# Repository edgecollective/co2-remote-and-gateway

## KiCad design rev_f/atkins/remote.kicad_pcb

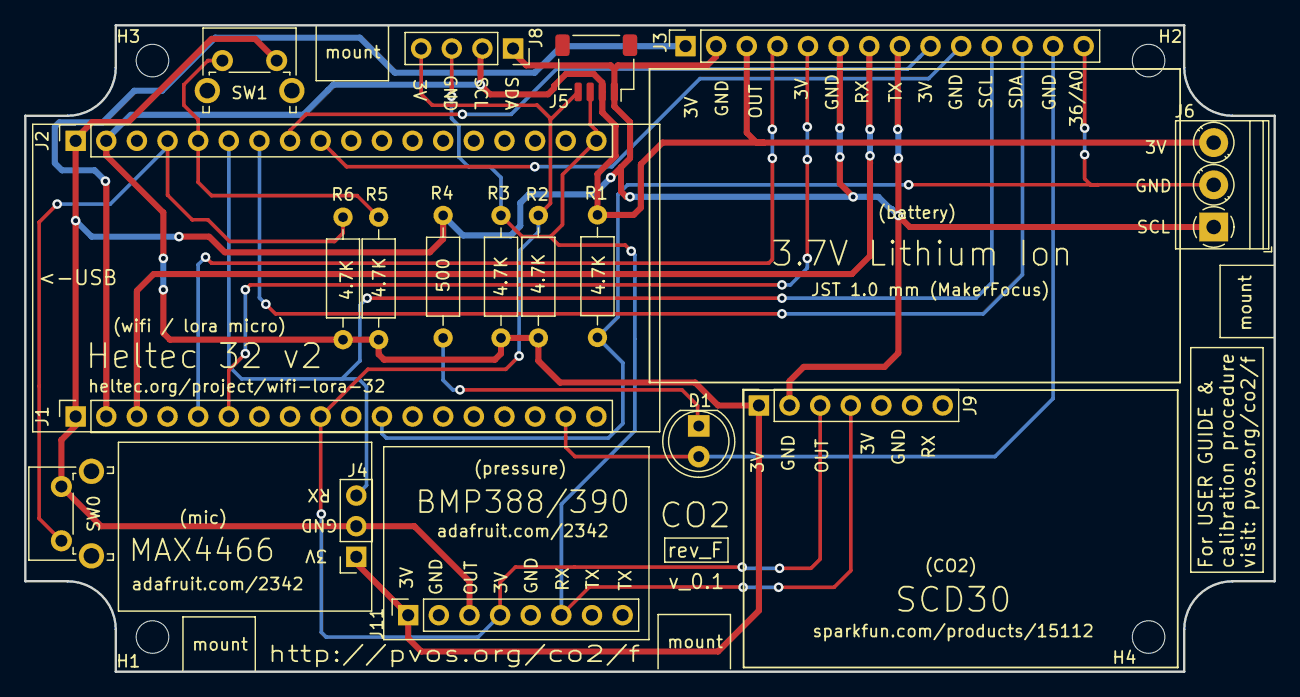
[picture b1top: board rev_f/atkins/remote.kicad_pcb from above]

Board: 2 copper layers, 103.6 x 53.6 mm, 22 parts (0 on the bottom side), 17 nets.

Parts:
D1: LED; LED_D5.0mm
H1, H2, H3, H4: MountingHole; MountingHole_2.7mm_M2.5
J1, J2: Conn_01x18_Female; PinSocket_1x18_P2.54mm_Vertical
J3: Conn_01x14_Female; PinSocket_1x14_P2.54mm_Vertical
J4: Conn_01x03_Female; PinSocket_1x03_P2.54mm_Vertical
J5: Conn_01x04_Female; JST_SH_SM04B-SRSS-TB_1x04-1MP_P1.00mm_Horizontal
J6: Screw_Terminal_01x03; TerminalBlock_Phoenix_PT-1,5-3-3.5-H_1x03_P3.50mm_Horizontal
J8: Conn_01x04_Female; PinSocket_1x04_P2.54mm_Vertical
J9: SCD30; PinSocket_1x07_P2.54mm_Vertical
J11: BME390; PinSocket_1x08_P2.54mm_Vertical
R1, R2, R3: R; R_Axial_DIN0207_L6.3mm_D2.5mm_P10.16mm_Horizontal
R4: 500R; R_Axial_DIN0207_L6.3mm_D2.5mm_P10.16mm_Horizontal
R5, R6: 4.7K; R_Axial_DIN0207_L6.3mm_D2.5mm_P10.16mm_Horizontal
SW0, SW1: SW_Push; SW_Tactile_SPST_Angled_PTS645Vx58-2LFS

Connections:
5V: J1.2, J3.1
17: D1.2, J1.17, J3.13
23: J1.11, J3.14, J6.2, R1.2
34_ADC6_DIO2: J2.8, J3.9
35_ADC7_DIO1: J2.9, J3.10
36_A0: J2.4, R6.2, SW0.1
37_A1: J2.5, R5.2, SW1.1
38_A2: J2.6, J3.11, J4.3
39_A3: J2.7, J3.12
+3V3: J2.2, J3.3, J4.1, J5.2, J6.3, J8.2, J9.1, J11.1, R1.1, R2.1, R3.1, R5.1, R6.1
GND: J1.1, J2.1, J3.2, J3.6, J3.8, J4.2, J5.1, J6.1, J8.1, J9.2, J11.3, R4.2, SW0.2, SW1.2
unnamed: D1.1, R4.1
RX: J1.5, J3.4
SCL: J1.9, J5.4, J8.4, J9.3, J11.4, R2.2
SDA: J2.18, J5.3, J8.3, J9.4, J11.6, R3.2
TX: J1.6, J3.5
VEXT: J1.3, J3.7

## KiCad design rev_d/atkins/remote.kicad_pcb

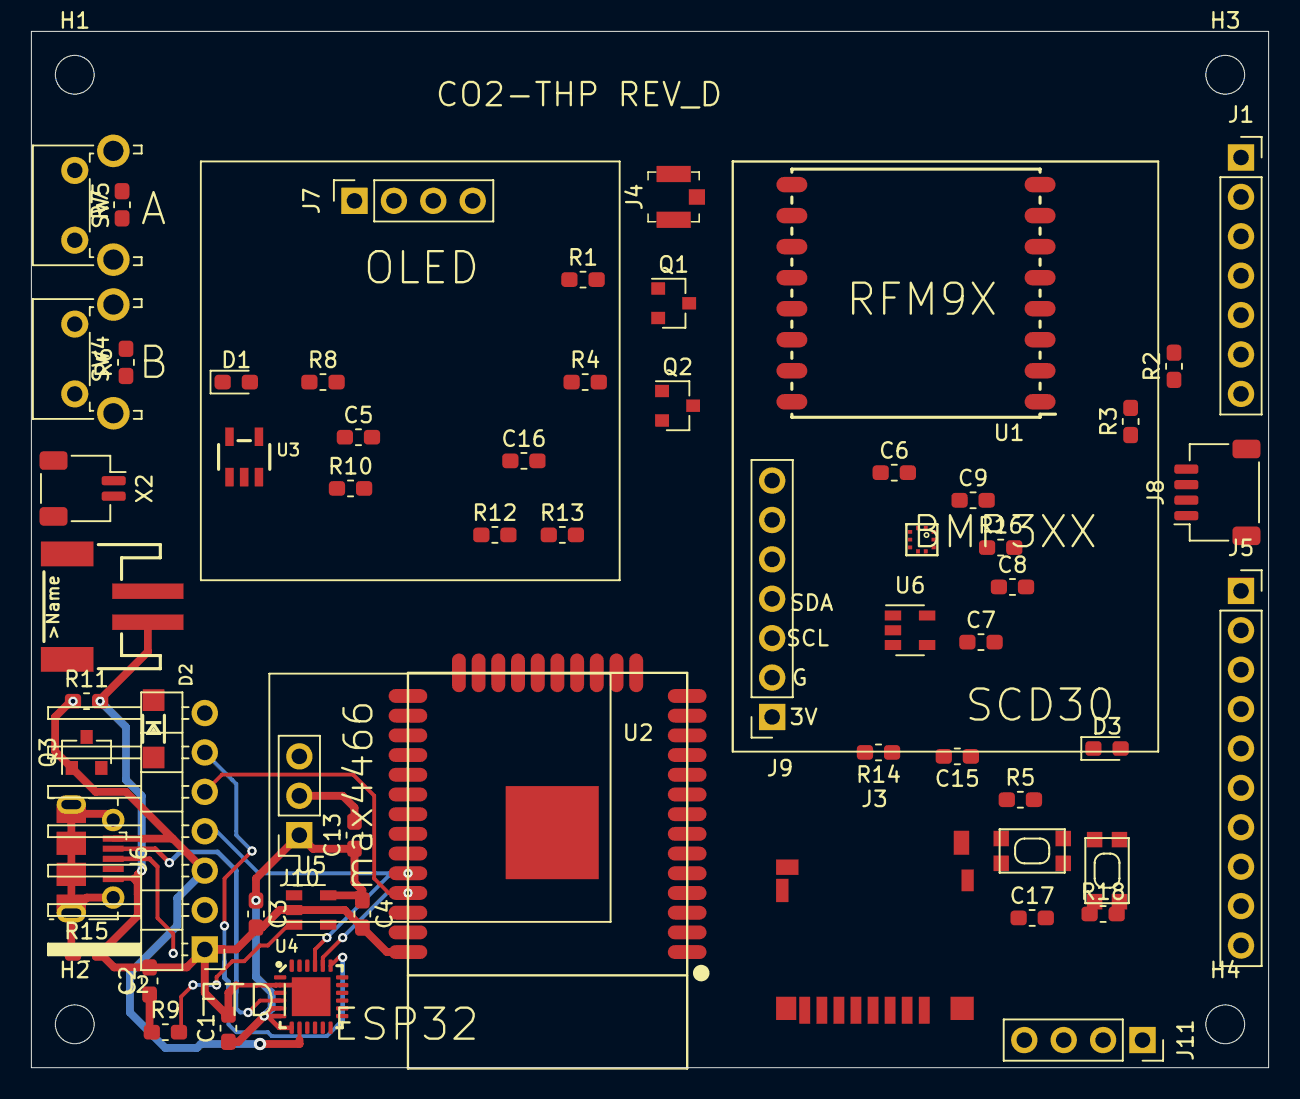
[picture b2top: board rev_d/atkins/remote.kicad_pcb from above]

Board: 2 copper layers, 79.8 x 66.8 mm, 64 parts (0 on the bottom side), 44 nets.

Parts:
C1, C2, C3, C6, C7: 10uF; C_0603_1608Metric_Pad1.05x0.95mm_HandSolder
C4, C8: 1uF; C_0603_1608Metric_Pad1.05x0.95mm_HandSolder
C5, C15, C17: C; C_0603_1608Metric_Pad1.05x0.95mm_HandSolder
C9, C13, C16: 0.1uF; C_0603_1608Metric_Pad1.05x0.95mm_HandSolder
D1, D3: LED; LED_0603_1608Metric_Pad1.05x0.95mm_HandSolder
D2: MBR120; SOD-123
H1, H2, H3, H4: MountingHole; MountingHole_2.5mm
J1: Conn_01x07_Female; PinSocket_1x07_P2.54mm_Vertical
J2: Conn_01x07_Female; PinHeader_1x07_P2.54mm_Horizontal
J3: Micro_SD_Card; DM3D-SF
J4: U_FL-R-SMT-1_10_; Coax_Conn_U.FL
J5: Conn_01x10_Female; PinSocket_1x10_P2.54mm_Vertical
J6: USB_B_Micro; USB_Micro-B_Molex-105017-0001
J7, J11: Conn_01x04_Female; PinSocket_1x04_P2.54mm_Vertical
J8: Conn_01x04_Male; JST_SH_SM04B-SRSS-TB_1x04-1MP_P1.00mm_Horizontal
J9: SCD30; PinSocket_1x07_P2.54mm_Vertical
J10: Conn_01x03_Female; PinSocket_1x03_P2.54mm_Vertical
Q1, Q2: Q_NPN_BEC; SOT-23
Q3: Q_PMOS_GSD - DMG3415U; SOT-23
R1, R2, R3, R4: R; R_0603_1608Metric_Pad1.05x0.95mm_HandSolder
R5, R6, R7, R10: 10K; R_0603_1608Metric_Pad1.05x0.95mm_HandSolder
R8: 1K; R_0603_1608Metric_Pad1.05x0.95mm_HandSolder
R9, R11, R16: 100K; R_0603_1608Metric_Pad1.05x0.95mm_HandSolder
R12, R13: 10M; R_0603_1608Metric_Pad1.05x0.95mm_HandSolder
R14, R15: 0 Ohm; R_0603_1608Metric_Pad1.05x0.95mm_HandSolder
R18: 500 Ohm; R_0603_1608Metric_Pad1.05x0.95mm_HandSolder
SW2, SW3: SPST_TACT-KMR2; KMR2
SW4, SW5: SW_Push; SW_Tactile_SPST_Angled_PTS645Vx58-2LFS
U1: RFM95HW; RFM95
U2: ESP32-WROOM
U3: MCP73831_2; SOT23-5
U4: CP2104; QFN24_4MM_SMSC
U5, U6: AP2112K-3.3; SOT-23-5
X1: CON_JST_PH_2PIN; JSTPH2
X2: CON_JST_PH_2PIN; JST_SH_SM02B-SRSS-TB_1x02-1MP_P1.00mm_Horizontal
u18: BMP388

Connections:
0: J11.1, Q1.3, SW2.2, SW2.4, U2.25
2: J11.2, U2.24
4: J11.3, U2.26
+3V3: C1.1, C3.1, C4.1, C7.1, C8.1, C9.1, C13.1, J1.5, J3.4, J7.2, J8.2, J9.1, J10.1, R2.1, R3.1, R6.1, R7.1, U1.13, U2.2, U4.5, U4.6, U4.7, U5.5, U6.5, u18.1, u18.10
A0_26_DAC0: J1.2, U2.11
A1_25_DAC1: J1.1, U2.10
A2_34: R7.2, SW5.2, U2.6
A7_32: R6.2, SW4.2, U2.8
A8_15: J10.3, U2.23
A11_12: D3.2, U2.14
A13_35: C16.1, R12.2, R13.1, U2.7
ANA: J4.2, U1.9
DTR: J2.7, Q1.2, R4.2, U4.23
GND: C1.2, C2.2, C3.2, C4.2, C5.2, C6.2, C7.2, C8.2, C9.2, C13.2, C15.2, C16.2, C17.2, J1.4, J2.1, J3.6, J4.1, J6.5, J7.1, J8.1, J9.2, J10.2, R11.2, R13.2, R15.2, R18.1, SW2.1, SW2.3, SW3.1, SW3.3, SW4.1, SW5.1, U1.1, U1.8, U1.10, U2.1, U2.38, U2.39, U4.2, U4.THERM, U5.2, U6.2, X1.1, X2.1, u18.3, u18.8, u18.9
MISO: J3.7, U1.2, U2.31
MOSI: J3.3, U1.3, U2.30
unnamed: C2.1, C6.1, Q3.2, R9.1, R16.1, U5.1, U6.1
unnamed: C15.1, R14.1
unnamed: D1.1, R8.2
unnamed: D3.1, R18.2
unnamed: J3.9, R14.2
unnamed: J6.2, U4.4
unnamed: J6.3, U4.3
unnamed: J6.6, R15.1
unnamed: Q1.1, R1.1
unnamed: Q2.1, R4.1
unnamed: R5.2, SW3.2, SW3.4
unnamed: R8.1, U3.1
unnamed: R9.2, U5.3
unnamed: R10.1, U3.2
unnamed: R10.2, U3.5
unnamed: R16.2, U6.3
RESET: C17.1, Q2.3, R5.1, U2.3
RTS: J2.6, Q2.2, R1.2, U4.19
RXD0: J2.4, U2.34, U4.21
SCK: J3.5, U1.4, U2.29
SCL: J1.7, J7.3, J8.4, J9.3, R2.2, U2.36, u18.2
SDA: J1.6, J7.4, J8.3, J9.4, R3.2, U2.37, u18.4
TXD0: J2.5, U2.35, U4.20
VBAT: C5.1, J11.4, Q3.3, R12.1, U3.3, X1.2, X2.2
VBUS: D1.2, J2.3, J6.1, Q3.1, R11.1, U3.4, U4.8
lora_cs: U1.5, U2.28
lora_dio0: U1.14, U2.27
lora_dio1: U1.15, U2.13, U2.16

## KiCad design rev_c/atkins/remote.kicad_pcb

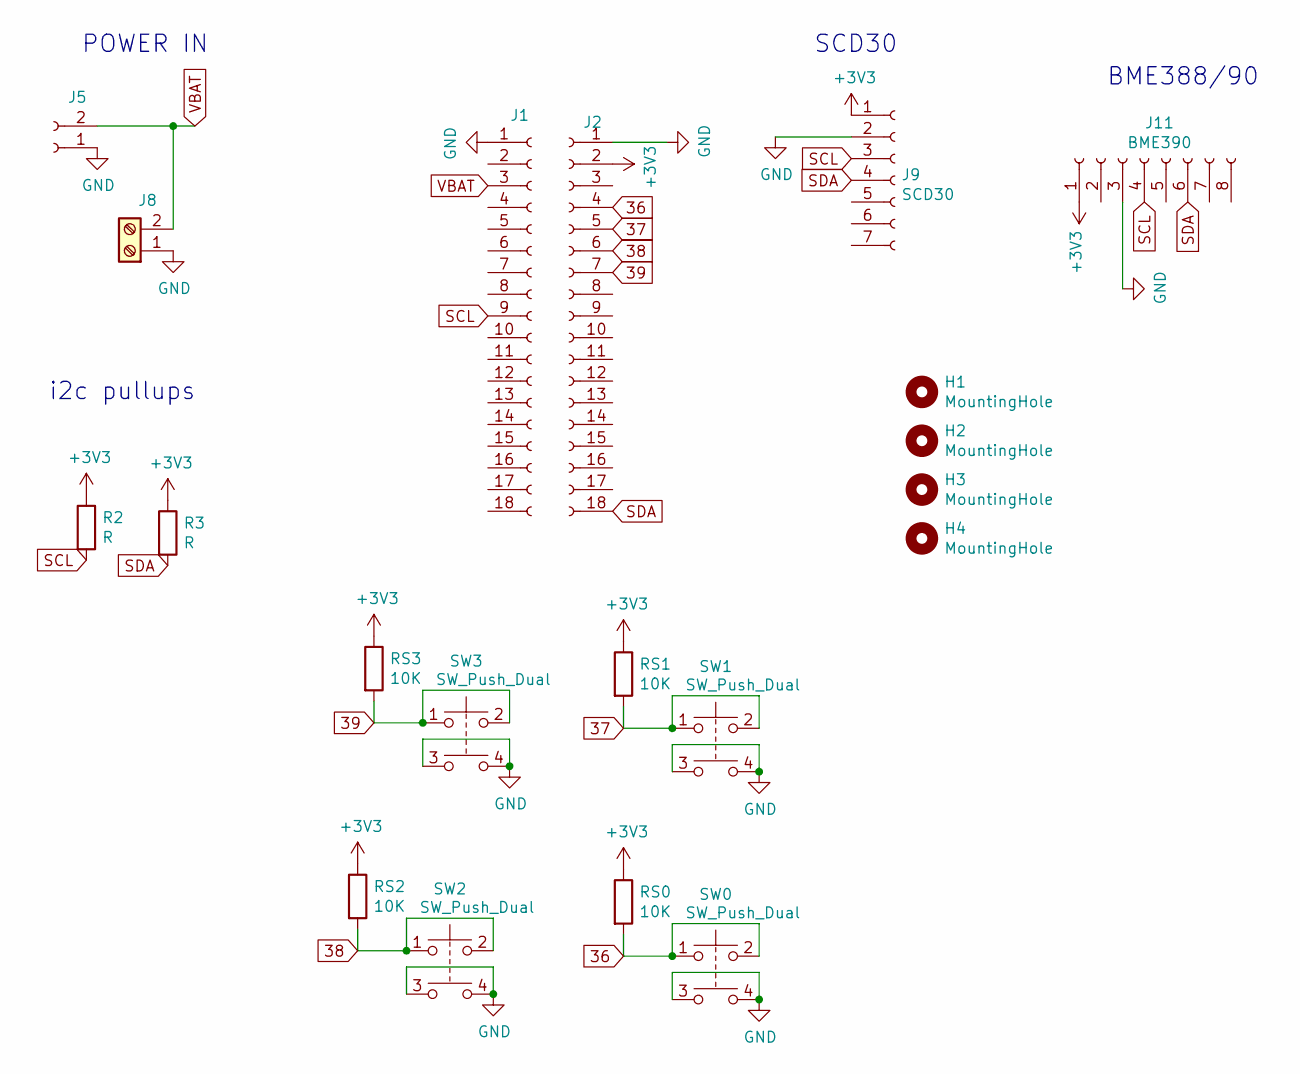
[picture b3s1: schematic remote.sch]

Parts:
H1, H2, H3, H4: MountingHole; MountingHole_2.7mm_M2.5
J1, J2: Conn_01x18_Female; PinSocket_1x18_P2.54mm_Vertical
J5: Conn_01x02_Female; PinSocket_1x02_P2.54mm_Vertical
J8: Screw_Terminal_01x02; TerminalBlock_Phoenix_MKDS-1,5-2_1x02_P5.00mm_Horizontal
J9: SCD30; PinSocket_1x07_P2.54mm_Vertical
J11: BME390; PinSocket_1x08_P2.54mm_Vertical
R2, R3: R; R_Axial_DIN0207_L6.3mm_D2.5mm_P10.16mm_Horizontal
RS0, RS1, RS2, RS3: 10K; R_Axial_DIN0207_L6.3mm_D2.5mm_P10.16mm_Horizontal
SW0, SW1, SW2, SW3: SW_Push_Dual; SW_TH_Tactile_Omron_B3F-10xx

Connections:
36: J2.4, RS0.2, SW0.1, SW0.2
37: J2.5, RS1.2, SW1.1, SW1.2
38: J2.6, RS2.2, SW2.1, SW2.2
39: J2.7, RS3.2, SW3.1, SW3.2
+3V3: J2.2, J9.1, J11.1, R2.1, R3.1, RS0.1, RS1.1, RS2.1, RS3.1
GND: J1.1, J2.1, J5.1, J8.1, J9.2, J11.3, SW0.3, SW0.4, SW1.3, SW1.4, SW2.3, SW2.4, SW3.3, SW3.4
SCL: J1.9, J9.3, J11.4, R2.2
SDA: J2.18, J9.4, J11.6, R3.2
VBAT: J1.3, J5.2, J8.2

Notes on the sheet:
POWER IN
i2c pullups
SCD30
BME388/90

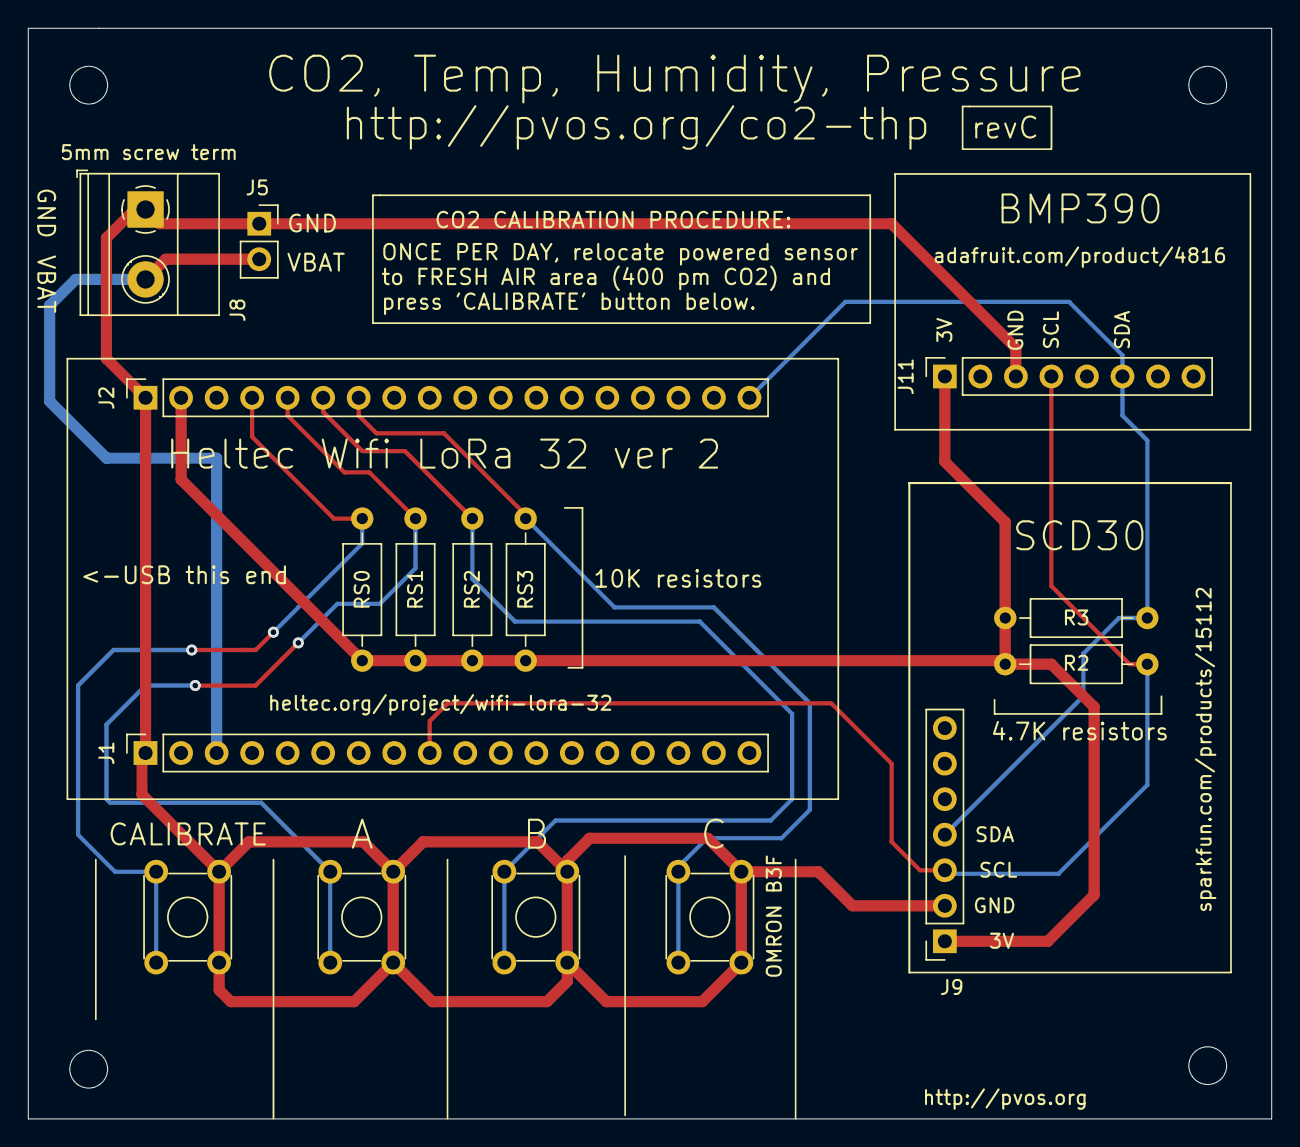
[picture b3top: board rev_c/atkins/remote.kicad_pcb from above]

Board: 2 copper layers, 88.9 x 78.0 mm, 20 parts (0 on the bottom side), 9 nets.

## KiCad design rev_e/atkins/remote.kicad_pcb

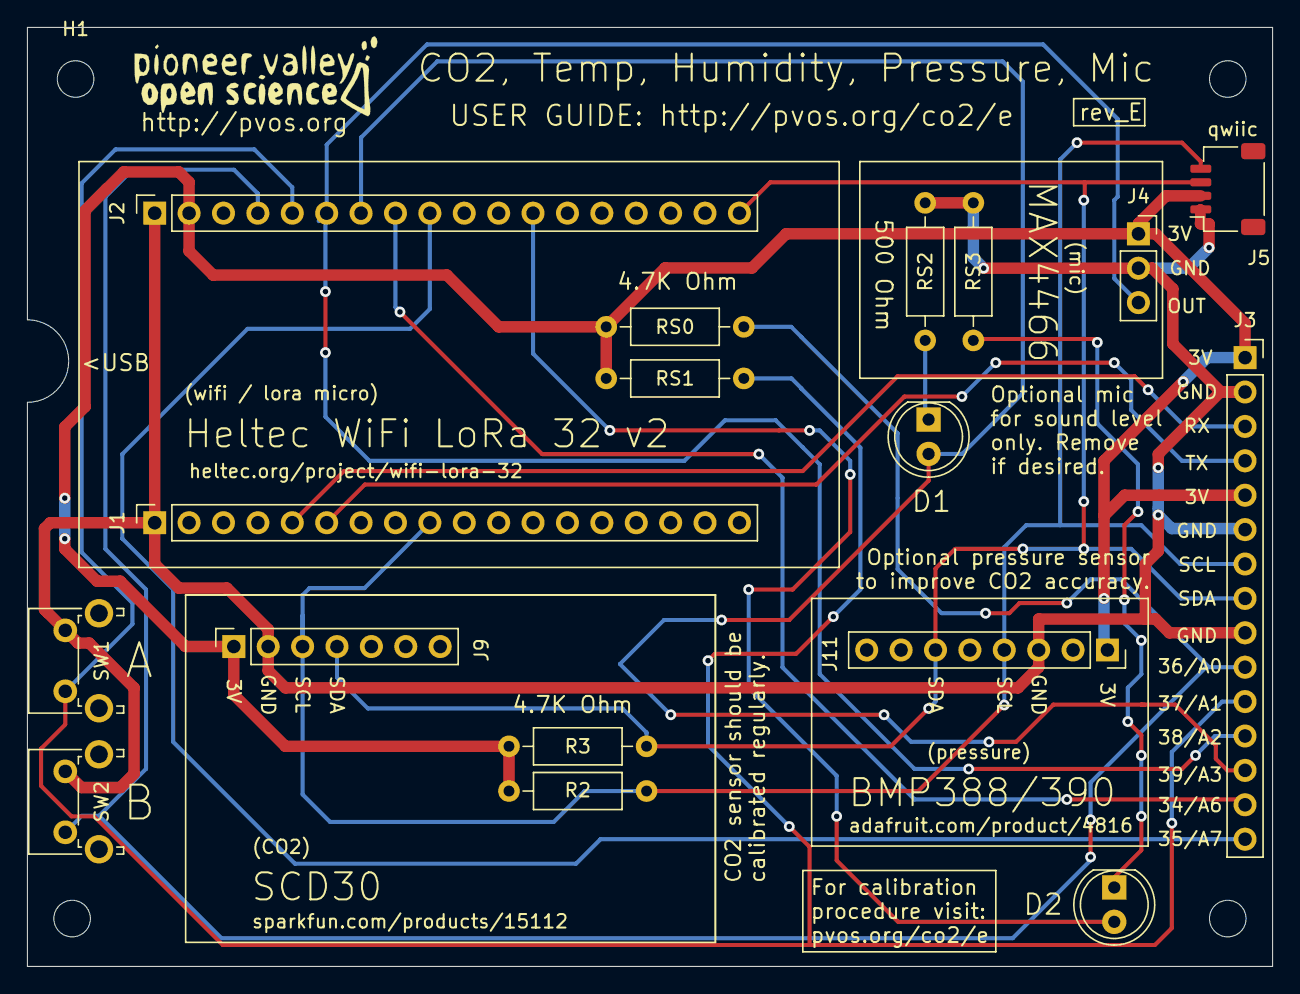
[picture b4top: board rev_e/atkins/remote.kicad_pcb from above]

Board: 2 copper layers, 91.9 x 69.3 mm, 21 parts (0 on the bottom side), 15 nets.

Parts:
D1, D2: LED; LED_D5.0mm
H1, H2, H3, H4: MountingHole; MountingHole_2.7mm_M2.5
J1, J2: Conn_01x18_Female; PinSocket_1x18_P2.54mm_Vertical
J3: Conn_01x15_Female; PinSocket_1x15_P2.54mm_Vertical
J4: Conn_01x03_Female; PinSocket_1x03_P2.54mm_Vertical
J5: Conn_01x04_Female; JST_SH_SM04B-SRSS-TB_1x04-1MP_P1.00mm_Horizontal
J9: SCD30; PinSocket_1x07_P2.54mm_Vertical
J11: BME390; PinSocket_1x08_P2.54mm_Vertical
R2, R3: R; R_Axial_DIN0207_L6.3mm_D2.5mm_P10.16mm_Horizontal
RS0, RS1: 10K; R_Axial_DIN0207_L6.3mm_D2.5mm_P10.16mm_Horizontal
RS2, RS3: 500R; R_Axial_DIN0207_L6.3mm_D2.5mm_P10.16mm_Horizontal
SW1, SW2: SW_Push; SW_Tactile_SPST_Angled_PTS645Vx58-2LFS

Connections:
25_LED: D2.2, J2.12
34_A6: J2.8, J3.14
35_A7: J2.9, J3.15
36_A0: J2.4, J3.10, RS0.2, SW2.1
37_A1: J2.5, J3.11, RS1.2, SW1.1
38_A2: J2.6, J3.12, J4.3
39_A3: D1.2, J2.7, J3.13
+3V3: J2.2, J3.1, J3.5, J4.1, J5.2, J9.1, J11.1, R2.1, R3.1, RS0.1, RS1.1
GND: J1.1, J2.1, J3.2, J3.6, J3.9, J4.2, J5.1, J9.2, J11.3, RS2.2, RS3.2, SW1.2, SW2.2
unnamed: D1.1, RS2.1
unnamed: D2.1, RS3.1
RX: J1.5, J3.3
SCL: J1.9, J3.7, J5.4, J9.3, J11.4, R2.2
SDA: J2.18, J3.8, J5.3, J9.4, J11.6, R3.2
TX: J1.6, J3.4

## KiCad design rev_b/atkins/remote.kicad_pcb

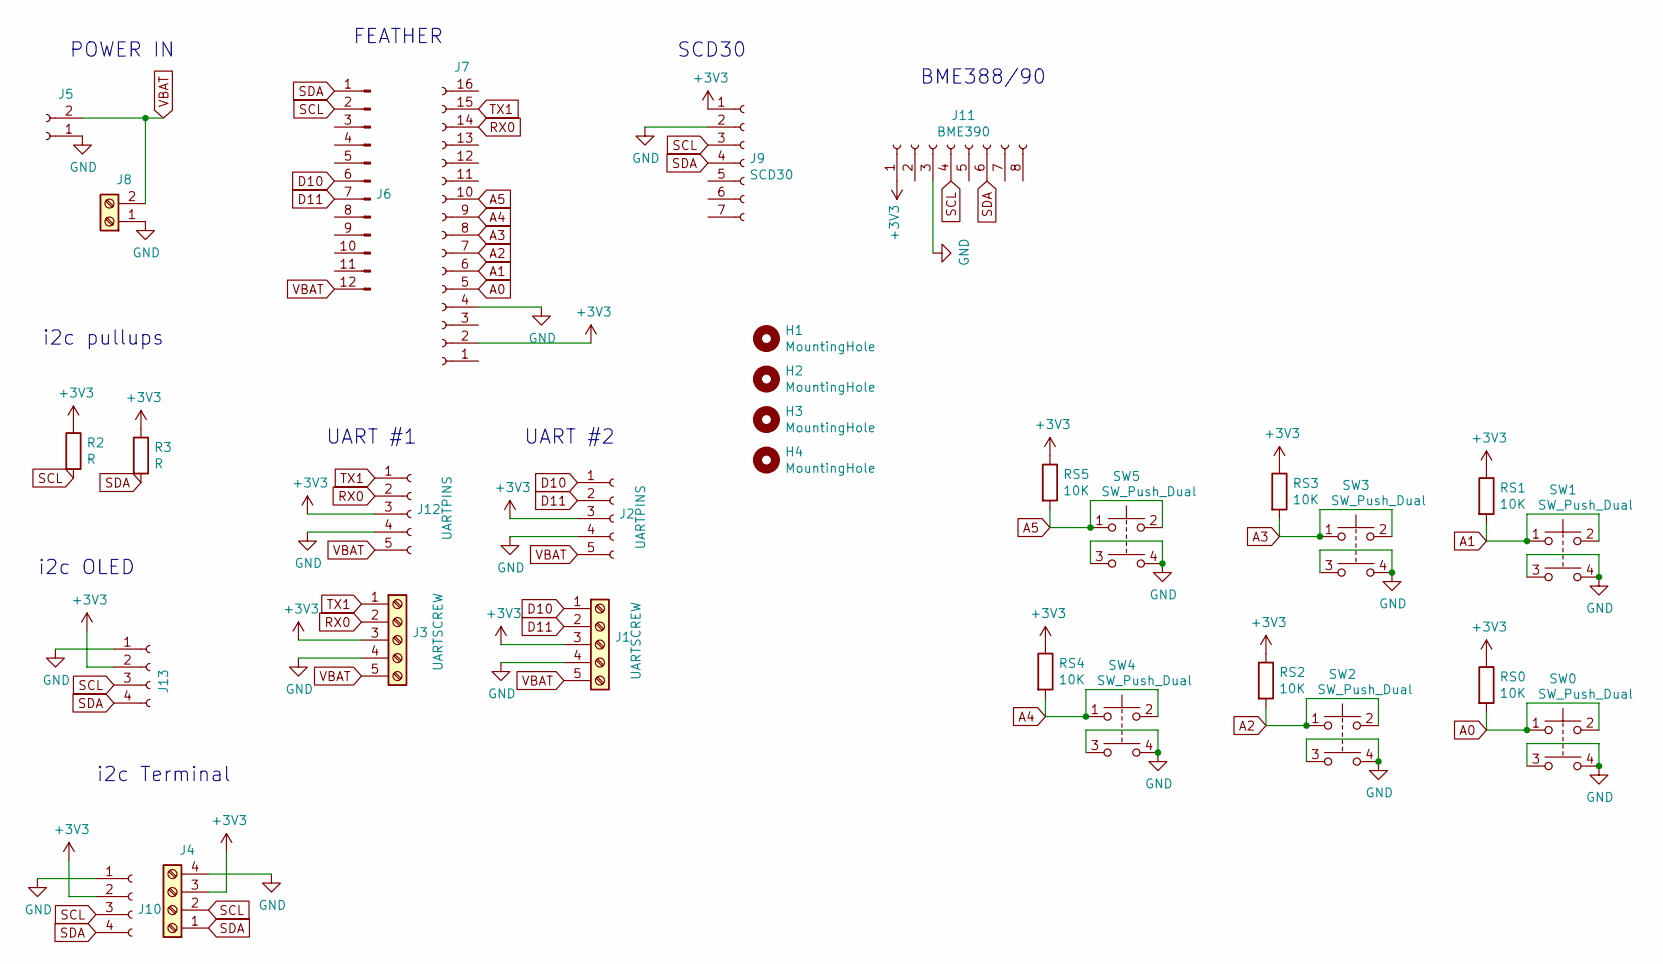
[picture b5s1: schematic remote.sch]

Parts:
H1, H2, H3, H4: MountingHole; MountingHole_2.7mm_M2.5
J1, J3: UARTSCREW; TerminalBlock_Phoenix_MKDS-1,5-5_1x05_P5.00mm_Horizontal
J2, J12: UARTPINS; PinSocket_1x05_P2.54mm_Vertical
J4: Screw_Terminal_01x04; TerminalBlock_Phoenix_MKDS-1,5-4_1x04_P5.00mm_Horizontal
J5: Conn_01x02_Female; PinSocket_1x02_P2.54mm_Vertical
J6: Conn_01x12_Male; PinSocket_1x12_P2.54mm_Vertical
J7: Conn_01x16_Female; PinSocket_1x16_P2.54mm_Vertical
J8: Screw_Terminal_01x02; TerminalBlock_Phoenix_MKDS-1,5-2_1x02_P5.00mm_Horizontal
J9: SCD30; PinSocket_1x07_P2.54mm_Vertical
J10, J13: Conn_01x04_Female; PinSocket_1x04_P2.54mm_Vertical
J11: BME390; PinSocket_1x08_P2.54mm_Vertical
R2, R3: R; R_Axial_DIN0207_L6.3mm_D2.5mm_P10.16mm_Horizontal
RS0, RS1, RS2, RS3, RS4, RS5: 10K; R_Axial_DIN0207_L6.3mm_D2.5mm_P10.16mm_Horizontal
SW0, SW1, SW2, SW3, SW4, SW5: SW_Push_Dual; SW_TH_Tactile_Omron_B3F-10xx

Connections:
+3V3: J1.3, J2.3, J3.3, J4.3, J7.2, J9.1, J10.2, J11.1, J12.3, J13.2, R2.1, R3.1, RS0.1, RS1.1, RS2.1, RS3.1, RS4.1, RS5.1
A0: J7.5, RS0.2, SW0.1, SW0.2
A1: J7.6, RS1.2, SW1.1, SW1.2
A2: J7.7, RS2.2, SW2.1, SW2.2
A3: J7.8, RS3.2, SW3.1, SW3.2
A4: J7.9, RS4.2, SW4.1, SW4.2
A5: J7.10, RS5.2, SW5.1, SW5.2
D10: J1.1, J2.1, J6.6
D11: J1.2, J2.2, J6.7
GND: J1.4, J2.4, J3.4, J4.4, J5.1, J7.4, J8.1, J9.2, J10.1, J11.3, J12.4, J13.1, SW0.3, SW0.4, SW1.3, SW1.4, SW2.3, SW2.4, SW3.3, SW3.4, SW4.3, SW4.4, SW5.3, SW5.4
RX0: J3.2, J7.14, J12.2
SCL: J4.2, J6.2, J9.3, J10.3, J11.4, J13.3, R2.2
SDA: J4.1, J6.1, J9.4, J10.4, J11.6, J13.4, R3.2
TX1: J3.1, J7.15, J12.1
VBAT: J1.5, J2.5, J3.5, J5.2, J6.12, J8.2, J12.5

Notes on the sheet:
UART #2
UART #1
POWER IN
FEATHER
i2c OLED
i2c Terminal
i2c pullups
SCD30
BME388/90

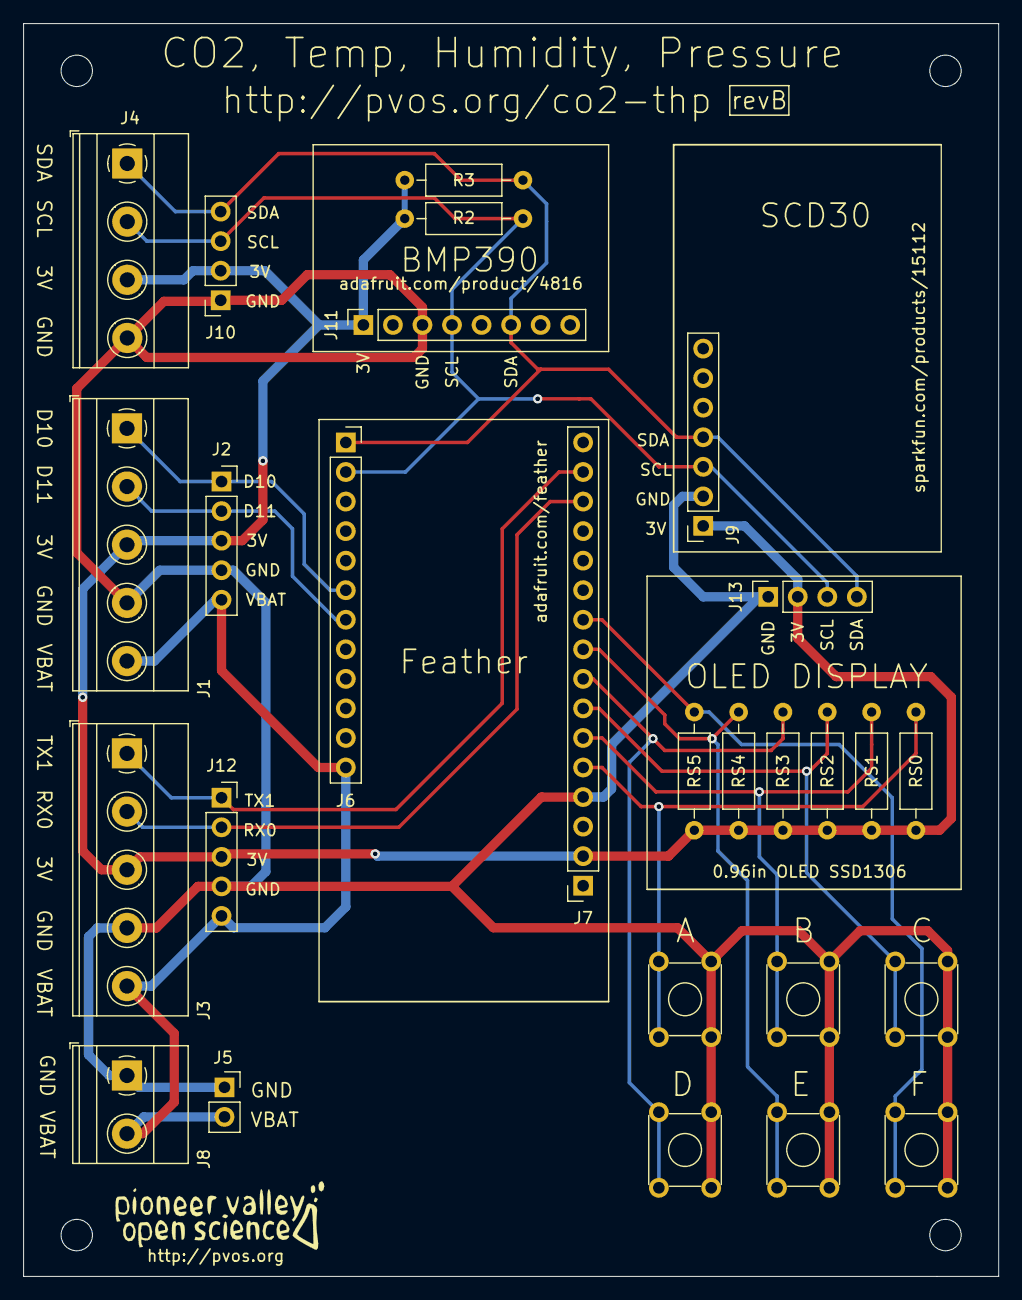
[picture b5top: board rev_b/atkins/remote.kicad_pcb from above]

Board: 2 copper layers, 83.8 x 107.7 mm, 31 parts (0 on the bottom side), 15 nets.

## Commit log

2020-12-15 jlcpcb order 14 dec 2020
2020-12-19 rev_d work
2020-12-24 update layout rev_d
2020-12-28 reparamterized so wall_thickness works
2020-12-28 redesigned to minkowski box shell geometry; orgin is bottom left corner of bounding box to facilitate measurement; NOTE that minkowski radius expands the cavity from its specified cubic dimensions, s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
2020-12-29 refactored hole coordinates; refactored to minkowski_dish module; added rim for lid with post corners (a bit wacky to do this)
2020-12-29 designed plate lid; drilled lid screw holes for M2.5 tap
2020-12-29 M2.5 pass through holes in lid and short taper in bottom
2020-12-29 M2.5 pass through holes for PCB mounting
2020-12-29 added button holes, screen, mic holes
2020-12-29 checked parts placements; modified heights of screen and mic objects to create holes in lid
2020-12-29 added comment
2020-12-29 added RTV gasket channel to walls
2020-12-30 added comments
2020-12-30 slight changes
2020-12-30 FIXED problems with minkowski_dish heights; ADDED wall mounting tabs; CHANGED pcb mounting hole for M2.5 tap; RESIZE lid for a 0.1mm gap fit; ADJUSTED heights for pcb specifications.
2020-12-30 updated STLs
2021-01-02 latest working wifi configuration example
2021-01-02 latest working wifi configuration example!
2021-01-02 added code for connecting to wifi and sending to a pre-flashed bayou url
2021-01-02 basic landing page functionality
2021-01-02 added some to landing page
2021-01-02 basic mvp where feed needs to be changed manually
2021-01-02 tweaked landing page a bit
2021-01-02 tweaked landing page again
2021-01-02 basic button functionality; also, made delay function more sensible, allows for more responsive esp32 ap server!
2021-01-03 added button functionality; also improved interface otherwise
2021-01-03 this uses elements.json as the configuration file. can expand from here
2021-01-03 closer to capturing feed data
2021-01-04 menu title tweaked
2021-01-06 changed endpoint names
2021-01-08 fully routed
2021-01-08 fixed labels
2021-01-08 moved buttons away from edge a bit
2021-01-08 added gerber files
